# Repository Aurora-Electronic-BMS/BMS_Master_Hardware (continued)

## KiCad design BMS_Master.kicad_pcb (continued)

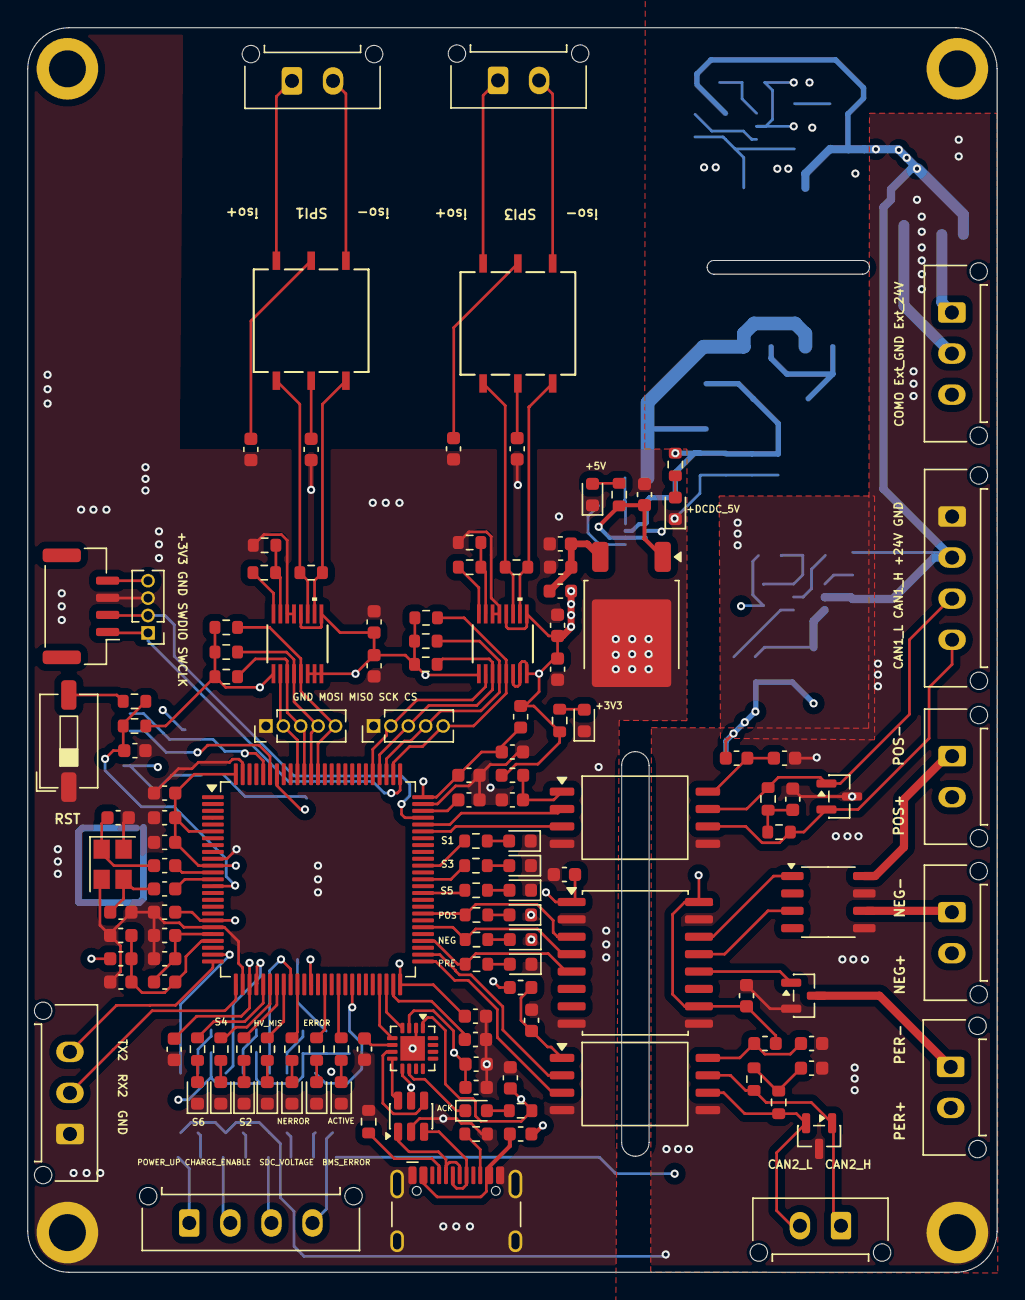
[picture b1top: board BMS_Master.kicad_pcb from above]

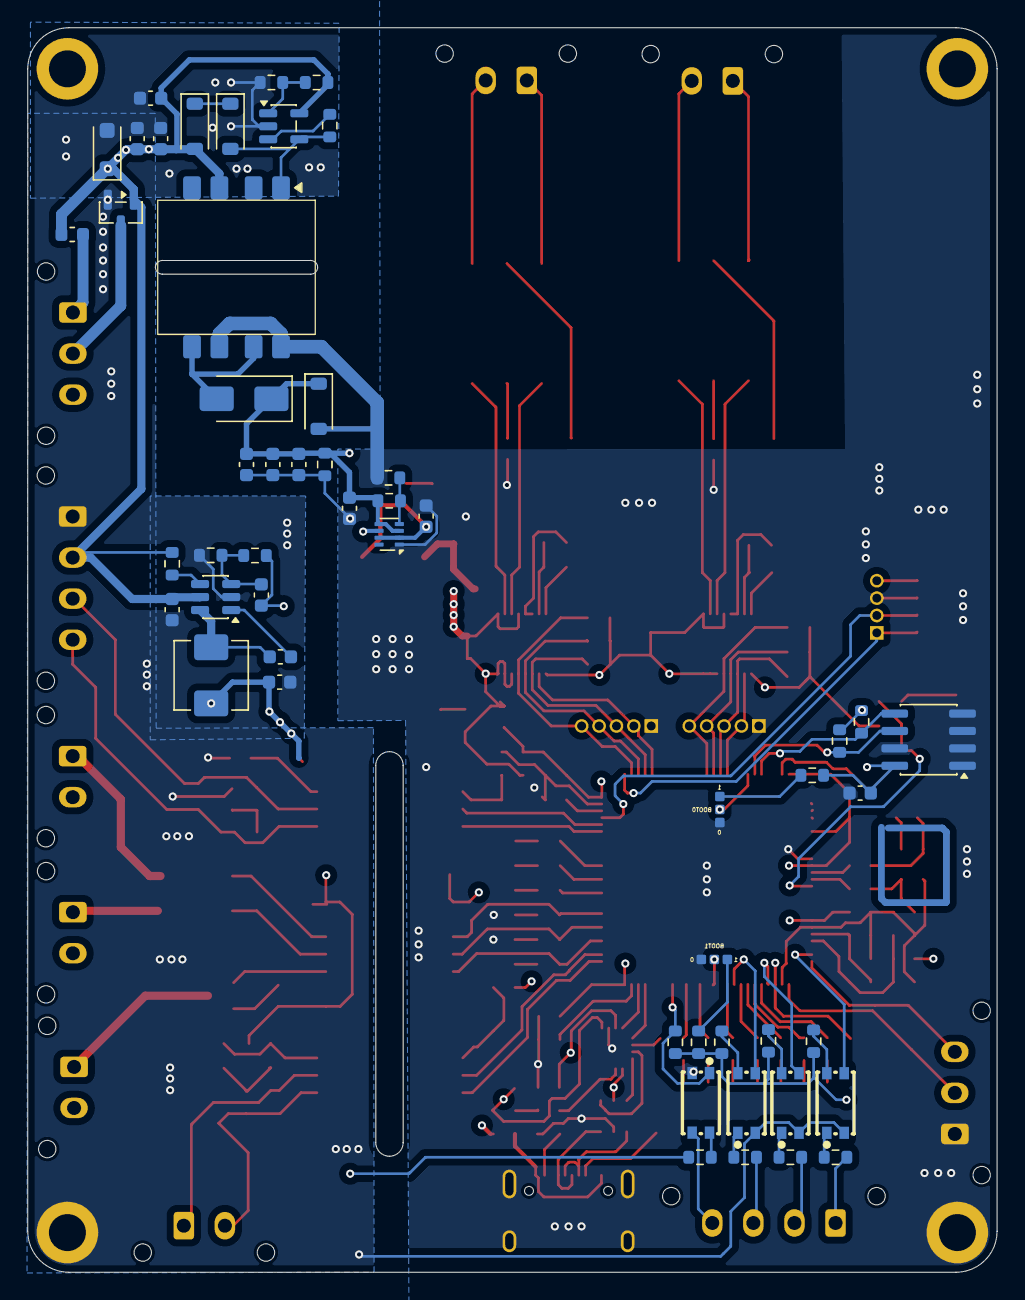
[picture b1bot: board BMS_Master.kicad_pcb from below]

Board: 4 copper layers, 70.8 x 90.9 mm, 194 parts (53 on the bottom side), 143 nets.

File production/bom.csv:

Designator,Footprint,Quantity,Value,LCSC Part #
"C1, C10, C11, C16, C17, C18, C2, C20, C21, C22, C24, C25, C26, C28, C29, C3, C30, C31, C32, C33, C34, C35, C36, C37, C38, C4, C43, C47, C50, C51",0603,30,100n,
"C12, C9",0603,2,1u,
C13,0603,1,4u7,
"C14, C15, C27, C44, C45",0603,5,10u,
"C19, C23, C52",0603,3,1uF,
"C39, C40",0603,2,2.2uF,
"C41, C42, C48",0603,3,22pF,
"C46, C49",0603,2,22u,
"C5, C6, C7, C8",0603,4,100pF,
C53,0603,1,2.2u,
"D1, D14, D15, D16, D17, D19",0603,6,BLUE,
"D10, D11, D12, D13",0603,4,GREEN,
D18,0603,1,WHITE,
D2,D_SOD-123,1,1N4148W,
"D20, D21",SOT-23,2,"PESD2CAN,215",
D22,D_SOD-123,1,BZT52C15,
D23,D_SMA,1,SS34,
D25,D_SOD-123,1,SMF6.0CA,
D3,D_SOD-123F,1,SMF36CA,
"D4, D6, D7, D8",0603,4,YELLOW,
"D5, D9",0603,2,RED,
"F1, F3",0603,2,1A,
F2,0603,1,2A,
"FB1, FB2, FB3, FB4, FB5",0603,5,60R@100MHz,
"H1, H2, H3, H4",MountingHole_2.7mm_M2.5_ISO14580_Pad,4,Mounting_Pad,
"J1, J2",boot,2,SolderJumper-predefined,
"J10, J3, J4, J7, J8, J9",Molex_Micro-Fit_3.0_43650-0215_1x02_P3.00mm_Vertical,6,Conn_01x02,
"J11, J13",Molex_Micro-Fit_3.0_43650-0415_1x04_P3.00mm_Vertical,2,Conn_01x04,
"J14, J6",Molex_Micro-Fit_3.0_43650-0315_1x03_P3.00mm_Vertical,2,Conn_01x03,
J16,PinHeader_1x04_P1.27mm_Vertical,1,Conn_01x04,
J17,JST_GH_BM04B-GHS-TBT_1x04-1MP_P1.25mm_Vertical,1,Conn_01x04,
"J20, J21",PinHeader_1x05_P1.27mm_Vertical,2,Conn_01x05,
J5,USB_C_Receptacle_HCTL_HC-TYPE-C-16P-01A,1,USB_C_Receptacle_USB2.0_16P,
L1,0603,1,600R@100MHz,
L2,L_Changjiang_FXL0530,1,4u7,
Q1,SOT-23,1,DMN61D8LQ,
Q2,SOT-23,1,2N7002K,
"R1, R2, R3, R4, R49, R5, R6",0603,7,10k,
"R10, R17, R46, R7, R8, R9",0603,6,1k,
"R11, R12",0603,2,120,
"R13, R14",0603,2,5k1,
"R15, R16, R23, R24, R25, R26, R27, R28, R29, R30, R31, R32, R33, R34, R35, R36, R37, R38",0603,18,3k3,
R18,0603,1,47,
"R19, R59, R61",0603,3,2k2,
"R39, R40, R52, R58, R60, R62",0603,6,4k7,
"R41, R42, R43, R44",0603,4,60,
"R45, R53, R54, R55, R57, R64",0603,6,100k,
R47,0603,1,0,
R48,0603,1,220,
R50,0603,1,15k,
R51,0603,1,470,
R56,0603,1,2k,
R63,0603,1,79k,
SW1,SW_DIP_SPSTx01_Slide_6.7x4.1mm_W6.73mm_P2.54mm_LowProfile_JPin,1,RESET,
"T1, T2",HM2103NL_PUL,2,HM2103NL,
T3,EE10,1,~,
"U1, U2",MS_05-08-1669_ADI,2,LTC6820HMS-TRPBF,
U10,SOIC-8_3.9x4.9mm_P1.27mm,1,AT24C521C,
"U11, U12",SOIC-8_7.5x5.85mm_P1.27mm,2,ISO1042,
U13,LQFP-100_14x14mm_P0.5mm,1,STM32F407VGT6,
"U14, U15, U16, U6",SMD-4_L4.5-W2.7-P1.27-LS4.9-TL,4,PS7802,
U17,SOT-23-6,1,PW2312,
U18,TSOT-23-5,1,JW3510,
U3,SOT-23-6,1,USBLC6-2SC6,
U4,WCH_QFN-16-1EP_3x3mm_P0.5mm_EP1.8x1.8mm,1,CH343P,
U5,SOT-583-8,1,TPS2116DRL,
U7,TO-252-2,1,LF33CDT-TR,
U8,SOIC-16W_7.5x10.3mm_P1.27mm,1,ISO7730FDWR,
U9,SOP-8_3.9x4.9mm_P1.27mm,1,NSD12409-Q1,
X1,Crystal_SMD_Abracon_ABM8AIG-4Pin_3.2x2.5mm,1,X3225  16MOB4SI,
